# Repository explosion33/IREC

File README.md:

# DomeCracker
This project implements an STM32 based flight computer with an onboard sensor suite. It features a custom PCB and embedded firmware to handle encoder reading, sensor interface and data logging in flight.

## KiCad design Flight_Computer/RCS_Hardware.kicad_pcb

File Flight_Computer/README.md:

# RCS_Hardware
SARP 2023 RCS Flight Controller KiCAD project

# Components
* STM32F401CCU6
* BNO055
* BMP280
* LIS2HH12 (TODO)
* W25Q32JVXX
* USB-C
* Battery Connector

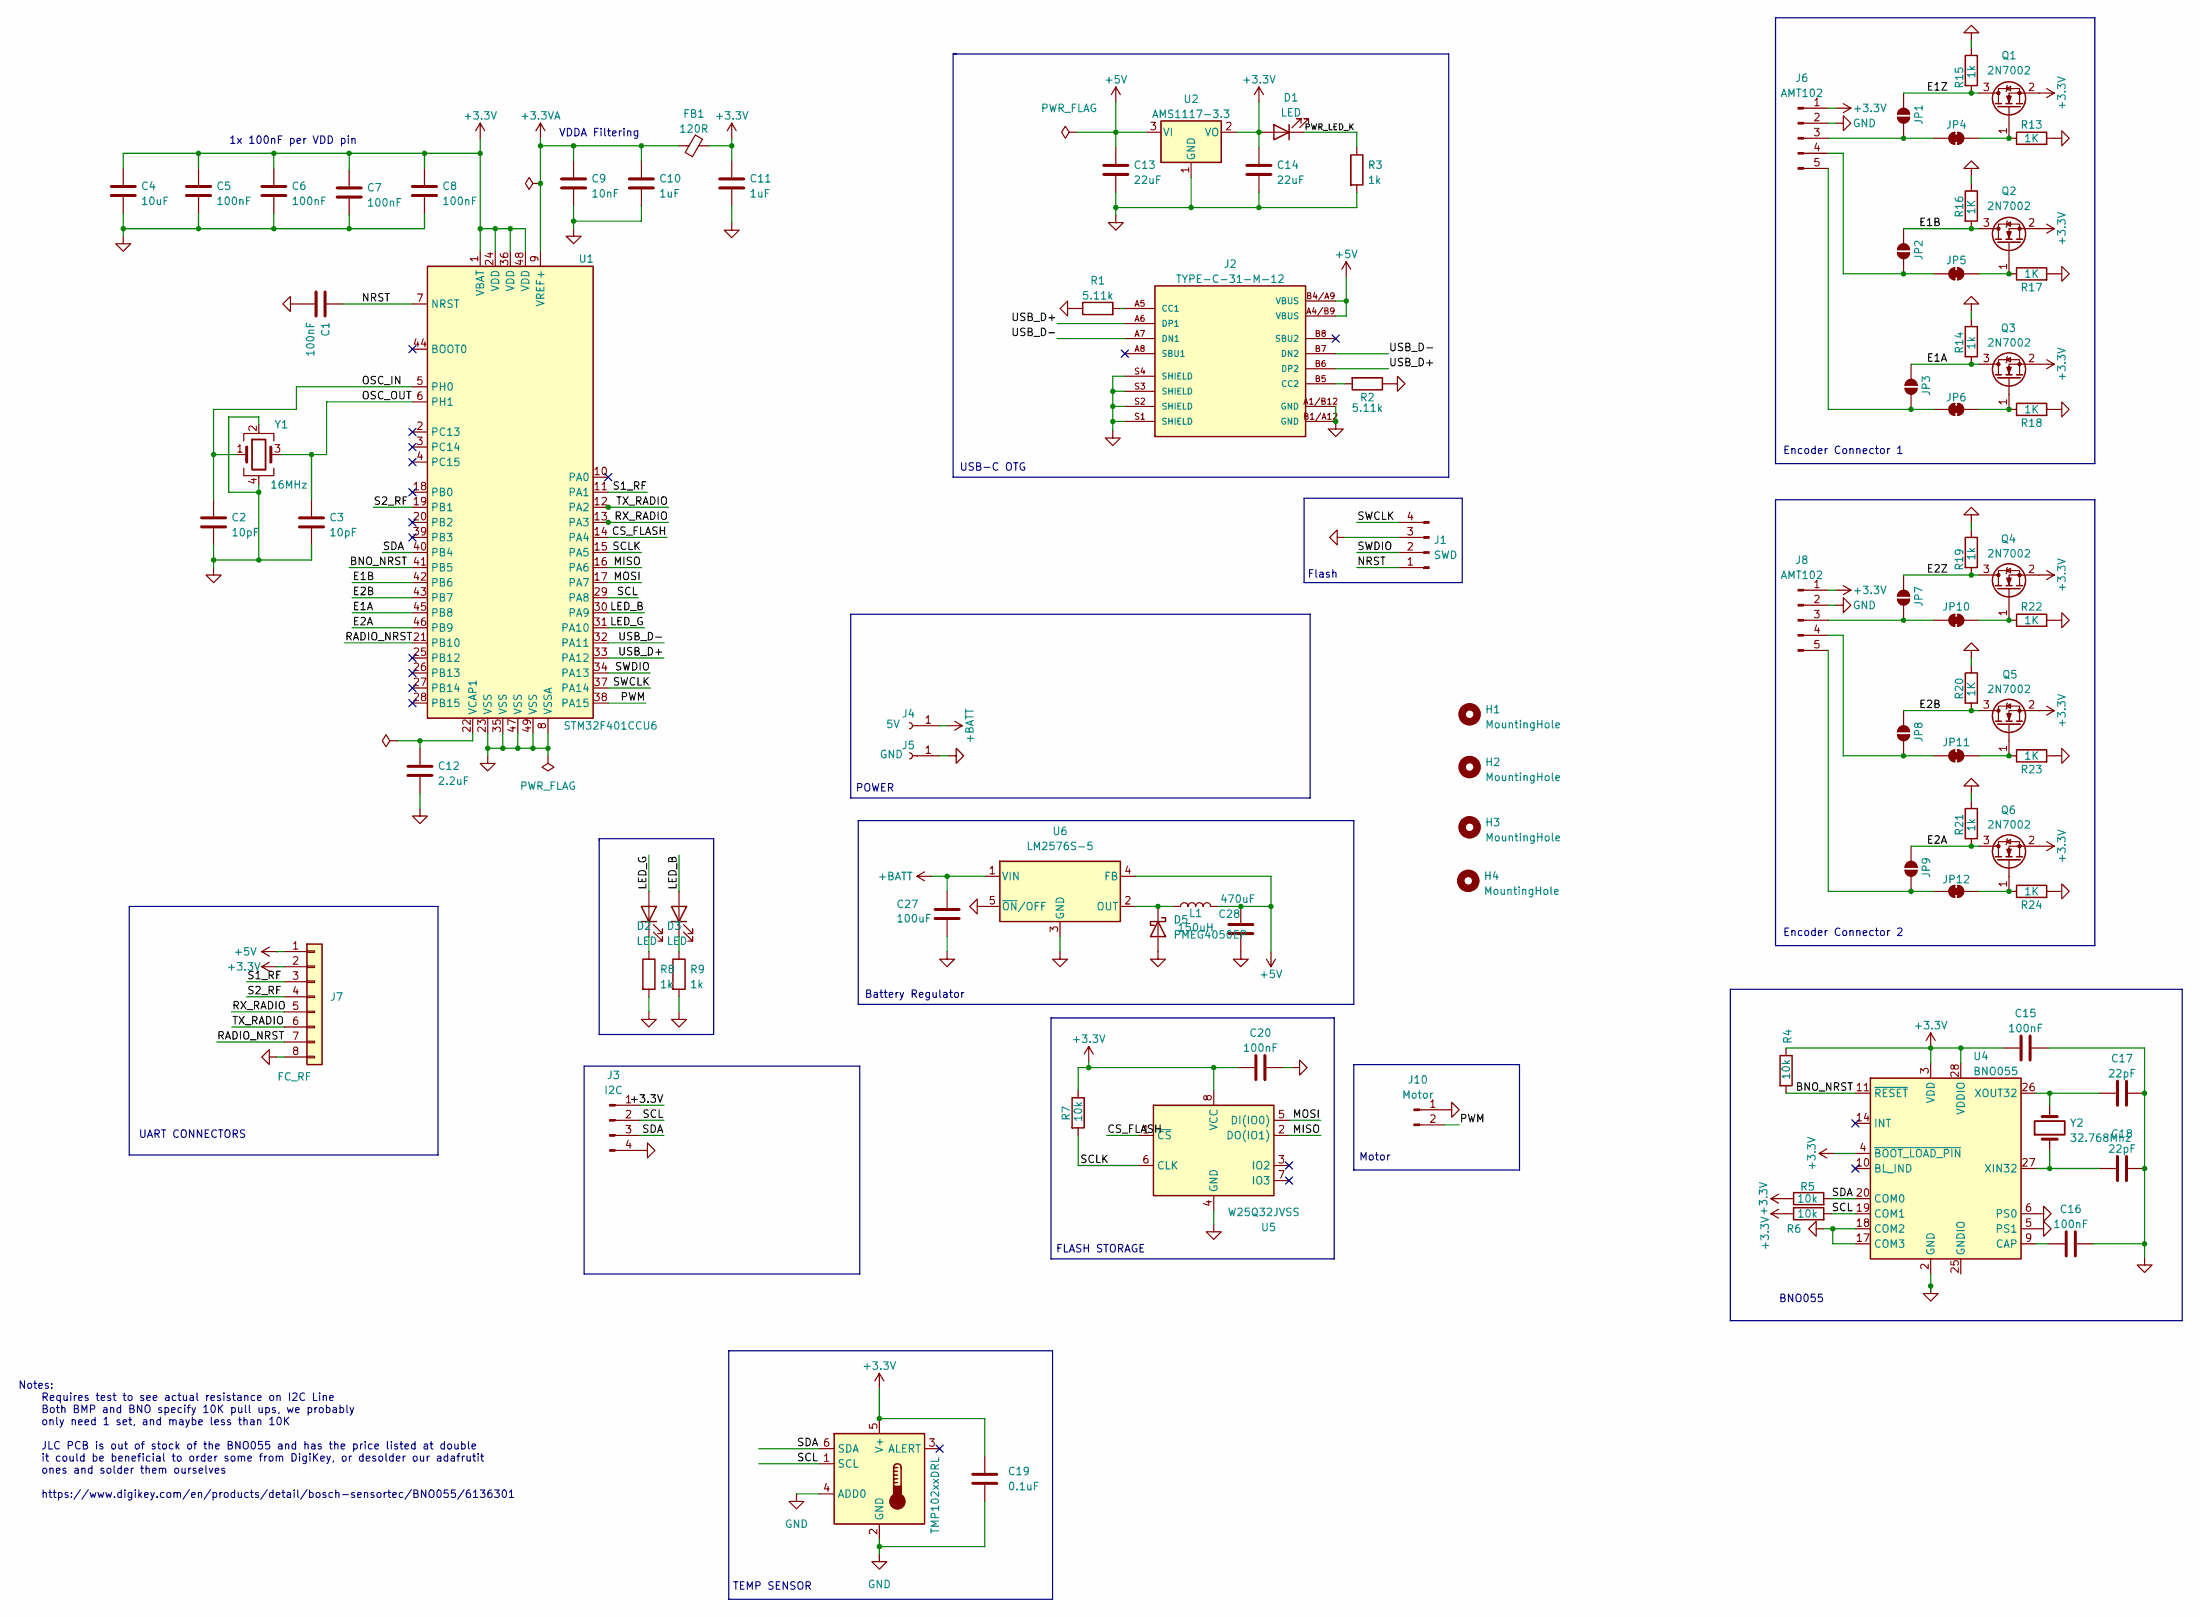
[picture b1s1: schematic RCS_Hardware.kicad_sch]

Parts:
C1, C5, C6, C7, C8, C15, C16, C20: 100nF; C_0402_1005Metric; JLCPCB# C307331
C2: 10pF; C_0402_1005Metric; JLCPCB# C32949
C3: 10pF; C_0402_1005Metric; LCSC Part C1525
C4: 10uF; C_0402_1005Metric; JLCPCB# C19702
C9: 10nF; C_0402_1005Metric; JLCPCB# C15195
C10, C11: 1uF; C_0402_1005Metric; JLCPCB# C52923
C12: 2.2uF; C_0402_1005Metric; JLCPCB# C12530
C13, C14: 22uF; C_0805_2012Metric; JLCPCB# C5674
C17, C18: 22pF; C_0402_1005Metric; JLCPCB# C466226
C19: 0.1uF; C_0402_1005Metric
C27: 100uF; C_0805_2012Metric; LCSC Part C141660
C28: 470uF; CP_Elec_10x10.5; LCSC Part C189257
D1, D2, D3: LED; LED_0603_1608Metric; JLCPCB# C273598
D5: PMEG4050EP; D_SOD-128
FB1: 120R; L_0603_1608Metric; JLCPCB# C85831
H1, H2, H3, H4: MountingHole; MountingHole_3.2mm_M3
J1: SWD; PinHeader_1x04_P2.54mm_Vertical
J2: TYPE-C-31-M-12; HRO_TYPE-C-31-M-12; PARTREV 2020.12.08; JLCPCB# C165948
J3: I2C; PinHeader_1x04_P2.54mm_Vertical
J4: 5V; TestPoint_THTPad_2.5x2.5mm_Drill1.2mm
J5: GND; TestPoint_THTPad_2.5x2.5mm_Drill1.2mm
J6, J8: AMT102; JST_SH_SM05B-SRSS-TB_1x05-1MP_P1.00mm_Horizontal
J7: FC_RF; Molex_200528-0080_1x08-1MP_P1.00mm_Horizontal; LCSC Part C505273
J10: Motor; JST_SH_SM02B-SRSS-TB_1x02-1MP_P1.00mm_Horizontal
JP1, JP2, JP3, JP7, JP8, JP9: SolderJumper_2_Open; SolderJumper-2_P1.3mm_Open_RoundedPad1.0x1.5mm
JP4, JP5, JP6, JP10, JP11, JP12: SolderJumper_2_Bridged; SolderJumper-2_P1.3mm_Bridged_RoundedPad1.0x1.5mm
L1: 150uH; L_TaiTech_TMPC1265_13.5x12.5mm; LCSC Part C408533
Q1, Q2, Q3, Q4, Q5, Q6: 2N7002; SOT-23; LCSC Part C466660
R1, R2: 5.11k; R_0402_1005Metric; JLCPCB# C25906
R3, R8, R9: 1k; R_0402_1005Metric; JLCPCB# C11702
R4, R5, R6, R7: 10k; R_0402_1005Metric; JLCPCB# C60490
R13, R16, R17, R18, R20, R22, R23, R24: 1K; R_0402_1005Metric
R14, R15, R19, R21: 1k; R_0402_1005Metric; LCSC Part C102758
U1: STM32F401CCU6; QFN-48-1EP_7x7mm_P0.5mm_EP5.6x5.6mm; JLCPCB# C79861
U2: AMS1117-3.3; SOT-223-3_TabPin2; JLCPCB# C6186
U3: TMP102xxDRL; SOT-563
U4: BNO055; LGA-28_5.2x3.8mm_P0.5mm; JLCPCB# C93216
U5: W25Q32JVSS; SOIC-8_5.23x5.23mm_P1.27mm; JLCPCB# C82344
U6: LM2576S-5; TO-263-5_TabPin3
Y1: 16MHz; Crystal_SMD_3225-4Pin_3.2x2.5mm; JLCPCB# C13738
Y2: 32.768Mhz; Crystal_SMD_3215-2Pin_3.2x1.5mm; JLCPCB# C907540

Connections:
+3.3V: C4.1, C5.1, C6.1, C7.1, C8.1, C11.1, C14.1, C15.1, C19.1, C20.1, D1.2 (A), FB1.2, J3.1, J6.1, J7.2, J8.1, Q1.2 (S), Q2.2 (S), Q3.2 (S), Q4.2 (S), Q5.2 (S), Q6.2 (S), R4.1, R5.1, R6.1, R7.1, U1.1 (VBAT), U1.24 (VDD), U1.36 (VDD), U1.48 (VDD), U2.2 (VO), U3.5 (V+), U4.3 (VDD), U4.4 (~BOOT_LOAD_PIN), U4.28 (VDDIO), U5.8 (VCC)
+3.3VA: C9.1, C10.1, FB1.1, U1.9 (VREF+)
+5V: C13.1, C28.2, J2.A4/B9 (VBUS), J2.B4/A9 (VBUS), J7.1, L1.2, U2.3 (VI), U6.4 (FB)
+BATT: C27.2, J4.1, U6.1 (VIN)
/BNO_NRST: R4.2, U1.41 (PB5), U4.11 (~RESET)
/CS_FLASH: U1.14 (PA4), U5.1 (~CS)
/E1A: JP3.2 (B), Q3.3 (D), R14.2, U1.45 (PB8)
/E1B: JP2.2 (B), Q2.3 (D), R16.2, U1.42 (PB6)
/E1Z: JP1.2 (B), Q1.3 (D), R15.2
/E2A: JP9.2 (B), Q6.3 (D), R21.2, U1.46 (PB9)
/E2B: JP8.2 (B), Q5.3 (D), R20.2, U1.43 (PB7)
/E2Z: JP7.2 (B), Q4.3 (D), R19.2
/LED_B: D3.2 (A), U1.30 (PA9)
/LED_G: D2.2 (A), U1.31 (PA10)
/MISO: U1.16 (PA6), U5.2 (DO(IO1))
/MOSI: U1.17 (PA7), U5.5 (DI(IO0))
/NRST: C1.1, J1.1, U1.7 (NRST)
/OSC_IN: C2.1, U1.5 (PH0), Y1.1
/OSC_OUT: C3.1, U1.6 (PH1), Y1.3
/PWM: J10.2, U1.38 (PA15)
/PWR_LED_K: D1.1 (K), R3.1
/RADIO_NRST: J7.7, U1.21 (PB10)
/RX_RADIO: J7.5, U1.13 (PA3)
/S1_RF: J7.3, U1.11 (PA1)
/S2_RF: J7.4, U1.19 (PB1)
/SCL: J3.2, R6.2, U1.29 (PA8), U3.1 (SCL), U4.19 (COM1)
/SCLK: R7.2, U1.15 (PA5), U5.6 (CLK)
/SDA: J3.3, R5.2, U1.40 (PB4), U3.6 (SDA), U4.20 (COM0)
/SWCLK: J1.4, U1.37 (PA14)
/SWDIO: J1.2, U1.34 (PA13)
/TX_RADIO: J7.6, U1.12 (PA2)
/USB_D+: J2.A6 (DP1), J2.B6 (DP2), U1.33 (PA12)
/USB_D-: J2.A7 (DN1), J2.B7 (DN2), U1.32 (PA11)
GND: C1.2, C2.2, C3.2, C4.2, C5.2, C6.2, C7.2, C8.2, C9.2, C10.2, C11.2, C12.2, C13.2, C14.2, C15.2, C16.2, C17.2, C18.2, C19.2, C20.2, C27.1, C28.1, D5.2 (A), J1.3, J2.A1/B12 (GND), J2.B1/A12 (GND), J2.S1 (SHIELD), J2.S2 (SHIELD), J2.S3 (SHIELD), J2.S4 (SHIELD), J3.4, J5.1, J6.2, J7.8, J8.2, J10.1, R1.1, R2.1, R3.2, R8.2, R9.2, R13.2, R14.1, R15.1, R16.1, R17.2, R18.2, R19.1, R20.1, R21.1, R22.2, R23.2, R24.2, U1.8 (VSSA), U1.23 (VSS), U1.35 (VSS), U1.47 (VSS), U1.49 (VSS), U2.1 (GND), U3.2 (GND), U3.4 (ADD0), U4.2 (GND), U4.5 (PS1), U4.6 (PS0), U4.17 (COM3), U4.18 (COM2), U5.4 (GND), U6.3 (GND), U6.5 (~ON/OFF), Y1.2, Y1.4
unnamed: D2.1 (K), R8.1
unnamed: D3.1 (K), R9.1
unnamed: D5.1 (K), L1.1, U6.2 (OUT)
unnamed: J2.A5 (CC1), R1.2
unnamed: J2.B5 (CC2), R2.2
unnamed: J6.3, JP1.1 (A), JP4.1 (A)
unnamed: J6.4, JP2.1 (A), JP5.1 (A)
unnamed: J6.5, JP3.1 (A), JP6.1 (A)
unnamed: J8.3, JP7.1 (A), JP10.1 (A)
unnamed: J8.4, JP8.1 (A), JP11.1 (A)
unnamed: J8.5, JP9.1 (A), JP12.1 (A)
unnamed: JP4.2 (B), Q1.1 (G), R13.1
unnamed: JP5.2 (B), Q2.1 (G), R17.1
unnamed: JP6.2 (B), Q3.1 (G), R18.1
unnamed: JP10.2 (B), Q4.1 (G), R22.1
unnamed: JP11.2 (B), Q5.1 (G), R23.1
unnamed: JP12.2 (B), Q6.1 (G), R24.1
unnamed: C12.1, U1.22 (VCAP1)
unnamed: C16.1, U4.9 (CAP)
unnamed: U4.15 (GNDIO), U4.16 (GNDIO), U4.25 (GNDIO)
unnamed: C18.1, U4.27 (XIN32), Y2.1
unnamed: C17.1, U4.26 (XOUT32), Y2.2

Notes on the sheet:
VDDA Filtering
Flash
FLASH STORAGE
Encoder Connector 1
UART CONNECTORS
Motor
1x 100nF per VDD pin
Notes: Requires test to see actual resistance on I2C Line Both BMP and BNO specify 10K pull ups, we probably only need 1 set, and maybe less than 10K JLC PCB is out of stock of the BNO055 and has the price listed at double it could be beneficial to order some from DigiKey, or desolder our adafrutit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
USB-C OTG
TEMP SENSOR
Encoder Connector 2
Battery Regulator
BNO055
POWER

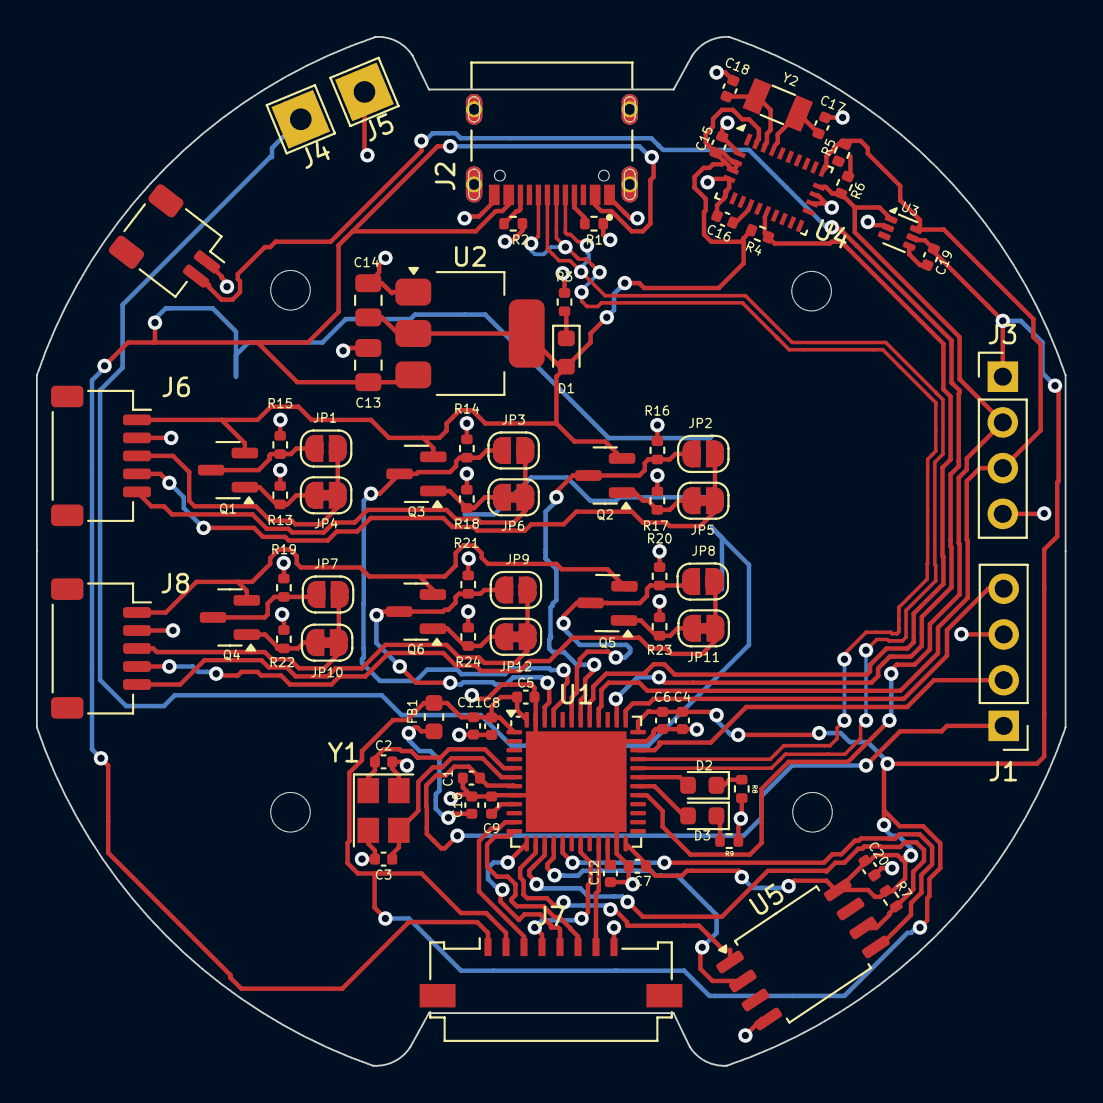
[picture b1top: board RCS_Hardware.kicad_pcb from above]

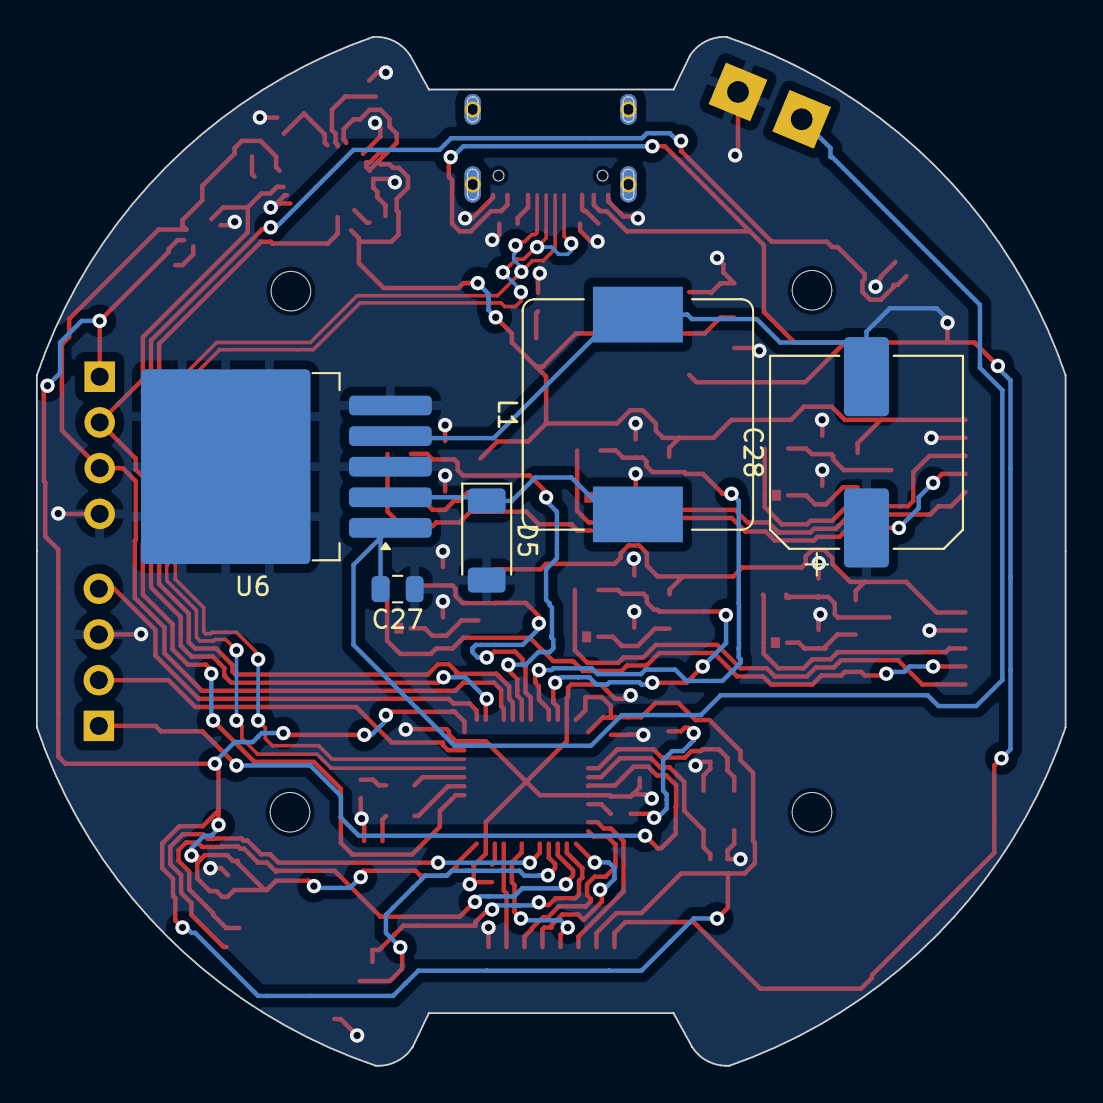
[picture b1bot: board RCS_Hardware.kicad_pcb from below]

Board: 2 copper layers, 57.2 x 57.2 mm, 88 parts (5 on the bottom side), 56 nets.

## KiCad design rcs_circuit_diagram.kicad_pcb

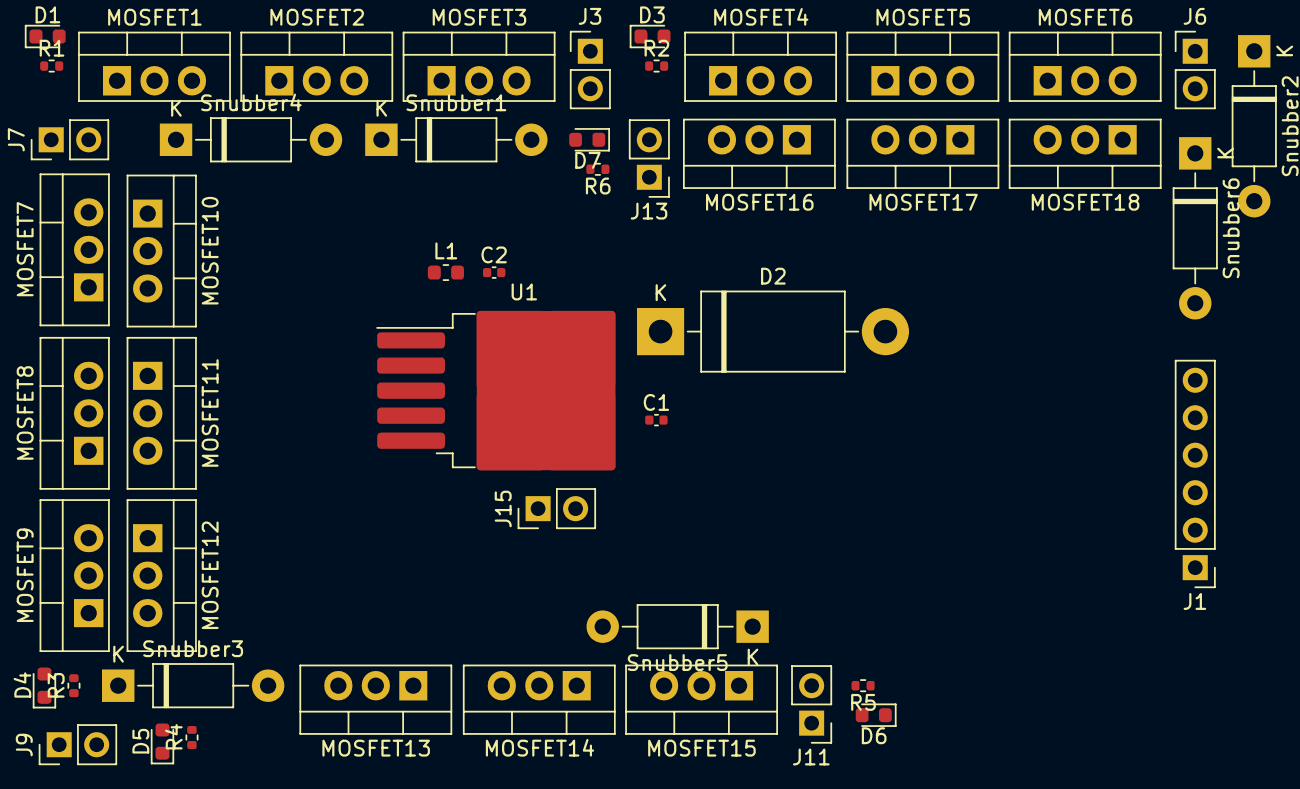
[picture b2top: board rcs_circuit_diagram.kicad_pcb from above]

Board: 2 copper layers, 49 parts (0 on the bottom side), 21 nets, no tracks yet.

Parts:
C1: 680 uF; C_0402_1005Metric
C2: 220 uF; C_0402_1005Metric
D1, D3, D4, D5, D6, D7: Red; LED_0603_1608Metric
D2: 1N5822; D_DO-201AD_P15.24mm_Horizontal
J1: Conn_01x06_Pin; PinHeader_1x06_P2.54mm_Vertical
J3, J6, J7, J9, J11, J13, J15: Conn_01x02_Pin; PinHeader_1x02_P2.54mm_Vertical
L1: 33 uH; L_0603_1608Metric
MOSFET1, MOSFET2, MOSFET3, MOSFET4, MOSFET5, MOSFET6, MOSFET7, MOSFET8, MOSFET9, MOSFET10, MOSFET11, MOSFET12, MOSFET13, MOSFET14, MOSFET15, MOSFET16, MOSFET17, MOSFET18: IRLB8721; TO-220-3_Vertical
R1, R2, R3, R4, R5, R6: 4.7k; R_0402_1005Metric
Snubber1, Snubber2, Snubber3, Snubber4, Snubber5, Snubber6: 1N5819; D_DO-41_SOD81_P10.16mm_Horizontal
U1: LM2596S-5; TO-263-5_TabPin3

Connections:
/sol2: J1.2, MOSFET4.1 (G), MOSFET5.1 (G), MOSFET6.1 (G)
/sol3: J1.3, MOSFET7.1 (G), MOSFET8.1 (G), MOSFET9.1 (G)
/sol4: J1.4, MOSFET16.1 (G), MOSFET17.1 (G), MOSFET18.1 (G)
/sol5: J1.5, MOSFET10.1 (G), MOSFET11.1 (G), MOSFET12.1 (G)
/sol6: J1.6, MOSFET13.1 (G), MOSFET14.1 (G), MOSFET15.1 (G)
GND: C1.2, C2.2, D2.2 (A), J6.2, MOSFET1.3 (S), MOSFET2.3 (S), MOSFET3.3 (S), MOSFET4.3 (S), MOSFET5.3 (S), MOSFET6.3 (S), MOSFET7.3 (S), MOSFET8.3 (S), MOSFET9.3 (S), MOSFET10.3 (S), MOSFET11.3 (S), MOSFET12.3 (S), MOSFET13.3 (S), MOSFET14.3 (S), MOSFET15.3 (S), MOSFET16.3 (S), MOSFET17.3 (S), MOSFET18.3 (S), U1.3 (GND), U1.5 (~ON/OFF)
unnamed: D1.2 (A), R1.2
unnamed: D1.1 (K), J3.1, MOSFET1.2 (D), MOSFET2.2 (D), MOSFET3.2 (D), Snubber1.2 (A)
unnamed: D2.1 (K), L1.1, U1.2 (OUT)
unnamed: D3.2 (A), R2.2
unnamed: D3.1 (K), J7.1, MOSFET4.2 (D), MOSFET5.2 (D), MOSFET6.2 (D), Snubber2.2 (A)
unnamed: D4.2 (A), R3.2
unnamed: D4.1 (K), J9.1, MOSFET7.2 (D), MOSFET8.2 (D), MOSFET9.2 (D), Snubber3.2 (A)
unnamed: D5.2 (A), R4.2
unnamed: D5.1 (K), J11.1, MOSFET10.2 (D), MOSFET11.2 (D), MOSFET12.2 (D), Snubber4.2 (A)
unnamed: D6.2 (A), R5.2
unnamed: D6.1 (K), J13.1, MOSFET13.2 (D), MOSFET14.2 (D), MOSFET15.2 (D), Snubber5.2 (A)
unnamed: D7.2 (A), R6.2
unnamed: D7.1 (K), J15.1, MOSFET16.2 (D), MOSFET17.2 (D), MOSFET18.2 (D), Snubber6.2 (A)
unnamed: J1.1, MOSFET1.1 (G), MOSFET2.1 (G), MOSFET3.1 (G)
VCC: C1.1, C2.1, J3.2, J6.1, J7.2, J9.2, J11.2, J13.2, J15.2, L1.2, R1.1, R2.1, R3.1, R4.1, R5.1, R6.1, Snubber1.1 (K), Snubber2.1 (K), Snubber3.1 (K), Snubber4.1 (K), Snubber5.1 (K), Snubber6.1 (K), U1.1 (VIN), U1.4 (FB)

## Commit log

2024-08-07 Copied flight computer over
2024-08-21 Add pull up resistor
2024-09-24 Pull old files
2024-09-24 Added rotary encoder symbol and schematic
2024-10-09 Added Uart and LM2576
2024-10-10 Added AS5601 and motor conn
2024-10-10 Motor connector
2024-10-17 Added new to do
2024-10-20 New battery circuit, updated encoders
2024-10-20 Level shifters
2024-10-20 Fixed encoders
2024-10-23 Plus BATT
2024-10-23 Moved some stuff around
2024-10-30 Encoder code
2024-11-07 Fixed encoder reading code
2024-11-21 added and started wiring temp sensor chip
2024-11-21 modified temp sensor connections
2024-11-27 added remaining footprints to gyroscope schematic and starting laying out components on PCB
2025-01-08 Created BNO055 LLibrary
2025-01-14 Blackpill setup
2025-01-20 Fixed wait funciton
2025-01-20 Added data read code
2025-01-21 Fixed .h file
2025-01-21 Marked Todos
2025-01-23 Fixing I2C functionality
2025-01-24 Fixed i2c stuff
2025-01-24 Fixed Write function
2025-01-25 Fixed stuff
2025-01-25 Added calibration functions
2025-01-25 stuff
2025-01-25 Ready to Test
2025-01-25 Fixed issues
2025-01-26 Created folders for encoder, tmp, flash
2025-01-29 temperature functions
2025-01-30 Moved constants to new file
2025-02-05 tmp code ready for testing
2025-02-06 motor drivers
2025-02-07 cleaned main
2025-02-10 updated gyroscope schematic
2025-02-11 placed components on gyroscope PCB
2025-02-11 moved usb-c connector position
2025-02-11 tmp functional
2025-02-12 routed most of pcb and updated encoder level-shifting circuit
2025-02-13 preliminary flash code
2025-02-20 Fixed motor tests
2025-02-25 updated encoder and motor connectors
2025-02-27 updated gyro schematic and started placing PCB
2025-02-28 finished (preliminary) placing of gyro pcb components
2025-02-28 bno055 tests
2025-02-28 tests
2025-03-05 BNO055 tested
2025-03-06 Encoder
2025-03-06 Encoder with I2C
2025-03-09 Cleaned up AS5601 code
2025-03-11 New encoder method
2025-03-13 TMP and flash tests passed
2025-03-31 Cleaning up code
2025-04-02 Added motor class
2025-04-02 Clean up code
2025-04-02 COM reader
2025-04-02 Deleted ESC
2025-04-04 Get ready to flash
2025-04-08 Added flash storage
2025-04-08 Fixed main
2025-04-08 updated targets & usb serial
2025-04-14 routed pcb
2025-04-15 test
2025-04-15 test worked
2025-04-15 Blackpill
2025-04-15 added part numbers for some footprints on pcb
2025-04-15 Working bno write to flash
2025-04-15 Created onboard functions
2025-04-18 New main
2025-04-18 todo
2025-04-22 Encoder fixes
2025-04-29 Added raw logging functions
2025-05-02 Added threads
2025-05-06 Added motor thread
2025-05-09 Tested
2025-05-12 Minor changes
2025-05-14 Optimizing for sensor rate
2025-05-16 Getting system code ready
2025-05-16 Added FSM stuff
2025-05-18 PCB Working
2025-05-18 Finished startup sequence
2025-05-19 added flash logging
2025-05-21 dummy main
2025-05-21 Test flight ready firmware
2025-05-22 flight ready
2025-05-23 Added led thread
2025-05-29 Fixed motor code
2025-05-29 Fixed motor class
2025-06-09 Final flight code
2025-06-10 Radio setup commands
2025-06-11 timeout, disable motor
2025-06-12 Cleaned Up files
